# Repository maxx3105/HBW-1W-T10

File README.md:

# HBW-1W-T10

10-Kanal-1-Wire-Temperaturmodul für HomeMatic Wired

## Überblick

HomeMatic-Wired-Gerät (RS485) mit bis zu 10 DS18x20-Temperatursensoren an einem
gemeinsamen 1-Wire-Bus. Die Sensoren werden **automatisch erkannt**: Beim Start
scannt das Gerät den Bus, übernimmt die ROM-Adressen jedes gefundenen Fühlers und
legt sie in freie Kanäle. In der CCU wird nur noch eingestellt, wann gesendet wird.

Gerätetyp `0x81`, Aufbau auf zwei Platinen (Hauptplatine und Bedienplatine).

### Basiert auf:
- **HBWired** von Thorsten Pferdekaemper: https://github.com/ThorstenPferdekaemper/HBWired
- Sketch-Vorlage von **loetmeister.de** (Thorsten Pferdekaemper, Dirk Hoffmann)
- Identify-LED nach einer Idee von **jfische**: https://github.com/jfische/HBW-1W-T10

## Aufbau des Repositories

```
HBW-1W-T10/
├── HBW-1W-T10/                  Arduino-Sketch (Ordnername muss zur .ino passen)
│   ├── HBW-1W-T10.ino
│   └── HBW-1W-T10_config.h      Pinbelegung dieser Platine
├── hbw_1w_t10_v1.xml            CCU-Gerätedefinition (hs485types)
├── PlatineA_CNMB2/              KiCad-Projekt Hauptplatine (+ Gerber)
├── PlatineB_CNMB2/              KiCad-Projekt Bedienplatine (+ Gerber)
└── README.md
```

## Hardware

### Unterstützte Sensoren

| Sensor | Family-Code | Auflösung | Genauigkeit |
|--------|-------------|-----------|-------------|
| **DS18B20** | 0x28 | 9–12 Bit (Werksvorgabe 12) | ±0,5 °C |
| **DS18S20** / DS1820 | 0x10 | 9 Bit + Extended Resolution | ±0,5 °C |
| **DS1822** | 0x22 | 9–12 Bit | ±2 °C |
| **DS1825** | 0x3B | 9–12 Bit | ±0,5 °C |

Bis zu 10 Fühler parallel an einem Bus (Daten, VCC, GND). DS18S20 wird intern
anders umgerechnet als die übrigen — er liefert 9 Bit in 0,5-°C-Schritten, die
über COUNT_REMAIN auf volle Auflösung hochgerechnet werden.

> **DS1825** setzt einen kleinen Patch in HBWired voraus, siehe [Installation](#2-ds1825-freischalten-optional).

### Bauteile

**PlatineA_CNMB2** (Hauptplatine)
- **ATmega328P-A** mit 16-MHz-Resonator
- **MAX487E** RS485-Transceiver (10 kΩ nach GND an TXEN, damit der Treiber beim
  Reset nicht sendet)
- **MC34063AD** Step-Down-Wandler (24 V Bus → 5 V), 270 µH, SB140
- Feinsicherung 375 mA, SM4007 Verpolschutz
- AVR-ISP-6 Programmierstecker
- Schraubklemmen für 24 V und Bus
- 4,7 kΩ Pull-up am 1-Wire-Bus, 100 kΩ Pull-up am Taster

**PlatineB_CNMB2** (Bedienplatine)
- Status-LED (rot) und Identify-LED (blau), je 470 Ω
- Taster für Config/Werksreset sowie Reset
- Steckverbinder zur Hauptplatine

## Pinbelegung

| Pin | Netz im Schaltplan | Funktion |
|-----|--------------------|----------|
| D2 | `TXEN` | RS485 Transmit-Enable |
| D10 | `1WIRE` | 1-Wire-Datenleitung (4,7 kΩ Pull-up nach VCC) |
| D12 / PB4 | `ID_LED` | Identify-LED |
| D13 | `LED` | Status-LED |
| A6 | `Button` | Taster für Config/Werksreset (100 kΩ Pull-up nach VCC, Taster gegen GND) |
| D0 / D1 | `RXD` / `TXD` | UART0 zum MAX487E |

Die SoftwareSerial-Variante von HBWired kommt hier
nicht in Frage (die bräuchte D2 als TX) — das Modul läuft mit
`USE_HARDWARE_SERIAL` über UART0.

**A6** ist beim ATmega328P im TQFP-Gehäuse ein reiner ADC-Eingang: kein
digitaler Eingangspuffer, kein interner Pull-up, `digitalRead()` funktioniert
dort nicht. HBWired erkennt das und fragt den Taster über `analogRead() < 250`
ab (rund 1,22 V bei 5 V), was den externen 100-kΩ-Pull-up auf der Hauptplatine
voraussetzt.

## Funktionsumfang

### Konfiguration je Kanal (in CCU/FHEM)

| Parameter | Bereich | Vorgabe | Bedeutung |
|-----------|---------|---------|-----------|
| **ONEWIRE_TYPE** | NOT_USED / DS18B20 / DS18S20 / DS1822 / DS1825 / REMOVE_SENSOR | NOT_USED | Anzeige des erkannten Sensortyps; `REMOVE_SENSOR` gibt den Kanal wieder frei |
| **SEND_DELTA_TEMP** | 0,1–25,0 °C | 0,5 °C | Sendet, sobald sich die Temperatur um diesen Betrag ändert |
| **OFFSET** | −1,27 bis +1,27 °C | 0,0 °C | Kalibrier-Offset (vorzeichenbehaftet, mit Bias 127 gespeichert) |
| **SEND_MIN_INTERVAL** | 5–3600 s | 10 s | Mindestabstand zwischen zwei Sendungen |
| **SEND_MAX_INTERVAL** | 5–3600 s | 150 s | Spätestens nach dieser Zeit wird gesendet |

### Konfiguration des Geräts

| Parameter | Vorgabe | Bedeutung |
|-----------|---------|-----------|
| **IDENTIFY_LED** | aus | LED an D12 blinkt im 600-ms-Takt, solange gesetzt — zum Auffinden des Moduls in der Verteilung |
| **OWN_ADDRESS** | 1 | Busadresse des Geräts |

### ONEWIRE_TYPE ist kein Einstellwert

Der Parameter liegt auf dem ersten Byte der 1-Wire-ROM-Adresse — dem Family-Code.
Er zeigt also an, was der Bus-Scan gefunden hat, und wird nicht von Hand gesetzt:
Ein hier eingetragener Typ ändert nur dieses eine Byte, die restlichen sieben
(Seriennummer und CRC) bleiben stehen, und der Kanal spricht danach eine Adresse
an, die es auf dem Bus nicht gibt.

Sinnvoll zu benutzen ist einzig **`REMOVE_SENSOR`**: Das schreibt 0xFF, macht die
gespeicherte Adresse ungültig und gibt den Kanal für einen neuen Fühler frei. Beim
Zurücklesen steht dort anschließend `NOT_USED` — es ist ein einmaliger Befehl,
kein Zustand.

### Ablauf

1. **Bus-Scan** bei jedem Start und nach jedem Konfigurationsschreiben der
   Zentrale: neue Sensoren wandern in freie Kanäle, ihre ROM-Adresse wird ins
   EEPROM übernommen.
2. **Messung**: Alle 1200 ms ist ein Kanal an der Reihe — erst Konvertierung
   anstoßen, im nächsten Durchgang das Ergebnis lesen. Es läuft immer nur eine
   Konvertierung gleichzeitig auf dem gemeinsamen Bus.
3. **Sendeentscheidung**: nie vor SEND_MIN_INTERVAL; gesendet wird bei einer
   Änderung ≥ SEND_DELTA_TEMP oder spätestens nach SEND_MAX_INTERVAL.

Die Kanalzuordnung ergibt sich aus der Reihenfolge, in der die Sensoren beim Scan
gefunden werden — und die hängt an den ROM-Adressen, nicht an der Position im
Strang. Wer eine bestimmte Zuordnung braucht, steckt die Fühler einzeln
nacheinander an oder räumt Kanäle gezielt über `REMOVE_SENSOR` frei.

## Installation

### 1. Arduino-IDE vorbereiten
```bash
git clone https://github.com/maxx3105/HBWired
# nach Arduino/libraries/HBWired kopieren
```

### 2. DS1825 freischalten (optional)

DS18B20, DS18S20 und DS1822 laufen mit HBWired unverändert. Für den **DS1825**
sind zwei kleine Ergänzungen in der Bibliothek nötig, da sie den Family-Code sonst
verwirft:

`libraries/src/HBWOneWireTempSensors.h`
```diff
     static const uint8_t DS18B20_ID = 0x28;
+    static const uint8_t DS1825_ID = 0x3B;
```

`libraries/src/HBWOneWireTempSensors.cpp`
```diff
 bool HBWOneWireTemp::deviceInvalidOrEmptyID(uint8_t deviceType) {
-  return !((deviceType == DS18B20_ID) || (deviceType == DS18S20_ID) || (deviceType == DS1822_ID));
+  return !((deviceType == DS18B20_ID) || (deviceType == DS18S20_ID) || (deviceType == DS1822_ID) ||
+           (deviceType == DS1825_ID));
 };
```

Die Umrechnung braucht keinen eigenen Zweig: Der DS1825 hält seine
Auflösungsbits an derselben Stelle wie der DS18B20 (`data[4] & 0x60`), womit der
bestehende `else`-Zweig greift.

### 3. Übersetzen und flashen

Der Sketch liegt im Unterordner `HBW-1W-T10/` (der Ordnername muss dem
`.ino`-Namen entsprechen).

- `HBW-1W-T10/HBW-1W-T10.ino` in der Arduino-IDE öffnen
- Board: **Arduino Nano** (ATmega328P)
- `HBW-1W-T10_config.h` bildet die Platine ab; `USE_HARDWARE_SERIAL` ist gesetzt.
  Zum Testen auf einem Nano mit Debug-Ausgabe auskommentieren.
- Flashen über ISP

Oder aus dem Projektverzeichnis heraus:

```
arduino-cli compile --fqbn arduino:avr:nano:cpu=atmega328 HBW-1W-T10
arduino-cli compile --fqbn arduino:avr:nano:cpu=atmega328 --upload --programmer usbasp HBW-1W-T10
```

Hinweis: Ist die EESAVE-Fuse nicht gesetzt, löscht jeder ISP-Flash das EEPROM —
und damit die Busadresse und alle gespeicherten Sensoradressen.

### 4. CCU/RaspberryMatic einrichten
1. https://github.com/maxx3105/JP-HB-Devices-addon
2. JP-HB-Devices-addon installieren
3. Gerät an den RS485-Bus anschließen
4. Anlernen und aus dem Posteingang übernehmen

## EEPROM-Belegung

`HBWDevice` liest die Konfigurationsstruktur ab EEPROM-Adresse `0x01`
(siehe `readConfig()` in HBWired.cpp), Struktur-Offset 6 landet also auf `0x07`.

```
0x00      : ungenutzt
0x01      : Logging-Zeit
0x02-0x05 : Zentralen-Adresse
0x06      : Bit 0 Direct-Link-Flag, Bit 1 Identify-LED (invertiert gespeichert)
0x07      : Kanal 1, Konfiguration (14 Byte)
  +0: send_delta_temp
  +1: offset (Bias 127: 0 = −1,27 °C, 127 = 0,00 °C, 254 = +1,27 °C)
  +2-3: send_min_interval (16 Bit, little endian)
  +4-5: send_max_interval (16 Bit, little endian)
  +6-13: 1-Wire-ROM-Adresse; Byte +6 ist der Family-Code = ONEWIRE_TYPE
0x15/0x23/... : Kanal 2..10, Konfiguration (Schrittweite 14), bis 0x92
0x3FC-0x3FF : OWN_ADDRESS (Busadresse, E2END−3 beim 1-kB-EEPROM des 328P)
```

Die Identify-LED wird **invertiert** abgelegt (`boolean_integer invert="true"` in
der XML): Nach einem Werksreset steht das EEPROM auf 0xFF, das Flag also auf 1 —
und die LED bleibt aus. Deshalb heißt das Feld im Sketch `n_identify_led`.

Ein `static_assert` in `HBW-1W-T10.ino` koppelt `ADDRESS_START_CONF_TEMP_CHAN` an
die tatsächliche Position von `TempOWCfg` in der Struktur. Käme ein Feld davor
hinzu, würde `sensorSearch()` sonst still in die Kanalkonfiguration schreiben —
der Build bricht stattdessen ab.

## Fehlersuche

### Sensoren werden nicht gefunden
- Verdrahtung prüfen (3-adrig, kein Parasite-Power-Betrieb vorgesehen)
- Nach dem Anstecken Reset drücken oder in der CCU die Konfiguration schreiben —
  beides löst einen Bus-Scan aus
- Fremde 1-Wire-Bausteine am Bus belegen kurzzeitig einen Kanal, bis ein echter
  Fühler den Platz übernimmt

### Temperatur zeigt −273,15 °C oder −273,14 °C
Das sind die beiden Sonderwerte der Firmware: **−273,15 °C** heißt „Kanal ohne
gültigen Sensor", **−273,14 °C** steht für einen Lese- oder CRC-Fehler, der drei
Versuche überdauert hat — typisch bei abgezogenem Fühler, zu langer Leitung oder
fehlendem Pull-up.

### Falsche Kanalzuordnung
Erwartungsgemäß: Die Reihenfolge kommt vom Bus-Scan, nicht von der Verdrahtung.
Über `REMOVE_SENSOR` einzelne Kanäle freiräumen und die Fühler nacheinander
anstecken.

### Gerät kommuniziert nicht
- RS485-Verdrahtung prüfen (A/B nicht vertauscht)
- Busadresse gesetzt? (`OWN_ADDRESS`, Seriennummer ist 7-Stellig und darf nur einmal am Bus vorhanden sein)
- Ist `USE_HARDWARE_SERIAL` aktiv? Ohne die Option belegt SoftwareSerial D2, das
  auf dieser Platine das Transmit-Enable ist.

### Modul in der Verteilung finden
`IDENTIFY_LED` in der Gerätekonfiguration setzen — die LED an D12 blinkt dann im
600-ms-Takt, bis der Haken wieder entfernt wird.

## Lizenz

Creative Commons BY-NC-SA 3.0 AT
http://creativecommons.org/licenses/by-nc-sa/3.0/at/

## Dank an

- Thorsten Pferdekaemper – HBWired-Framework
- Dirk Hoffmann – Beiträge zu HBWired
- loetmeister.de – Sketch-Vorlage HBW-1W-T10
- jfische – Idee der Identify-LED

## Änderungsverlauf

### v0.06
- 1-Wire-Busarbitrierung repariert: Die Kanäle hielten Zeiger auf lokale
  Variablen von `setup()`, deren Speicher freigegeben wird, sobald `loop()`
  läuft (auch upstream eingereicht:
  [HBWired#47](https://github.com/ThorstenPferdekaemper/HBWired/pull/47))
- `static_assert` koppelt die Kanaladresse an das Struktur-Layout

### v0.05
- DS1825 als vierter Sensortyp

### v0.04
- Identify-LED an D12, schaltbar über den Geräteparameter `IDENTIFY_LED`

### v0.03
- Prüfung auf unterstützte Sensortypen
- Konvertierungs- und Messablauf entzerrt, um falsche Messwerte zu vermeiden

### v0.02
- Start und Fehlerbehandlung bei abgezogenen Sensoren verbessert

### v0.01
- Erste Fassung

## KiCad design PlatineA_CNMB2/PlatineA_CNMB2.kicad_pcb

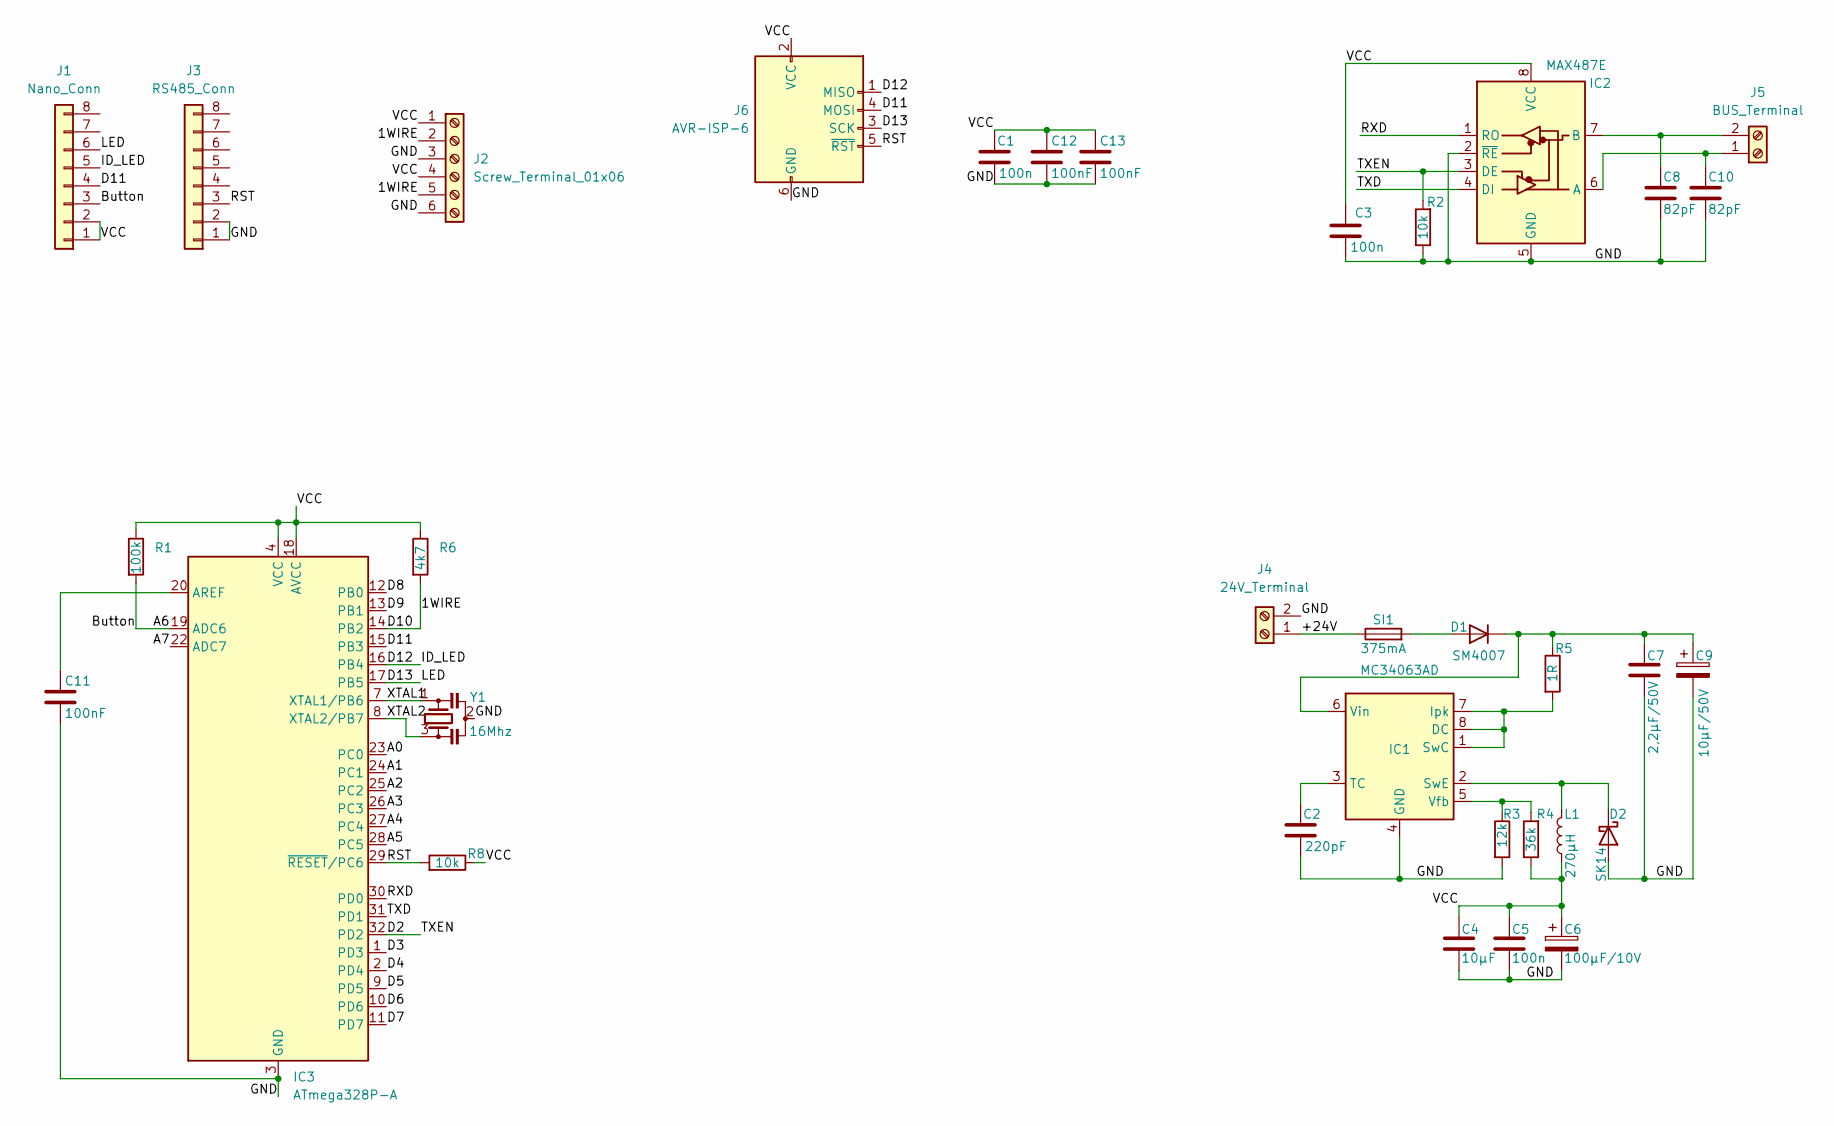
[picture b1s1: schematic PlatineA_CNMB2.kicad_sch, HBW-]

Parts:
C1, C3, C5: 100n; C_0805_2012Metric_Pad1.18x1.45mm_HandSolder
C2: 220pF; C_0805_2012Metric_Pad1.18x1.45mm_HandSolder
C4: 10µF; C_1210_3225Metric_Pad1.33x2.70mm_HandSolder
C6: 100µF/10V; CP_Radial_D5.0mm_P2.50mm
C7: 2,2µF/50V; C_1210_3225Metric_Pad1.33x2.70mm_HandSolder
C8, C10: 82pF; C_0805_2012Metric_Pad1.18x1.45mm_HandSolder
C9: 10µF/50V; CP_Radial_D5.0mm_P2.50mm
C11, C12, C13: 100nF; C_0805_2012Metric_Pad1.18x1.45mm_HandSolder
D1: SM4007; D_MELF
D2: SK14; D_SMA_Handsoldering
IC1: MC34063AD; SOIC-8_3.9x4.9mm_P1.27mm
IC2: MAX487E; SOIC-8_3.9x4.9mm_P1.27mm
IC3: ATmega328P-A; TQFP-32_7x7mm_P0.8mm
J1: Nano_Conn; PinHeader_1x08_P2.54mm_Vertical
J2: Screw_Terminal_01x06; TerminalBlock_bornier-6_P5.08mm
J3: RS485_Conn; PinHeader_1x08_P2.54mm_Vertical
J4: 24V_Terminal; TerminalBlock_bornier-2_P5.08mm
J5: BUS_Terminal; TerminalBlock_bornier-2_P5.08mm
J6: AVR-ISP-6; PinHeader_2x03_P2.54mm_Vertical
L1: 270µH; L_Taiyo-Yuden_MD-4040
R1: 100k; R_0805_2012Metric_Pad1.20x1.40mm_HandSolder
R2, R8: 10k; R_0805_2012Metric_Pad1.20x1.40mm_HandSolder
R3: 12k; R_0805_2012Metric_Pad1.20x1.40mm_HandSolder
R4: 36k; R_0805_2012Metric_Pad1.20x1.40mm_HandSolder
R5: 1R; R_0805_2012Metric_Pad1.20x1.40mm_HandSolder
R6: 4k7; R_0805_2012Metric_Pad1.20x1.40mm_HandSolder
SI1: 375mA; FUSC6127X294N
Y1: 16Mhz; Resonator_SMD_Murata_CSTxExxV-3Pin_3.0x1.1mm_HandSoldering

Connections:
/1WIRE: IC3.14 (PB2), J2.2, J2.5, R6.2
/+24V: J4.1, SI1.1
/A0: IC3.23 (PC0)
/A1: IC3.24 (PC1)
/A2: IC3.25 (PC2)
/A3: IC3.26 (PC3)
/A4: IC3.27 (PC4)
/A5: IC3.28 (PC5)
/A6: IC3.19 (ADC6), J1.3, R1.2
/A7: IC3.22 (ADC7)
/D2: IC2.3 (DE), IC3.32 (PD2), R2.2
/D3: IC3.1 (PD3)
/D4: IC3.2 (PD4)
/D5: IC3.9 (PD5)
/D6: IC3.10 (PD6)
/D7: IC3.11 (PD7)
/D8: IC3.12 (PB0)
/D9: IC3.13 (PB1)
/D11: IC3.15 (PB3), J1.4, J6.4 (MOSI)
/D12: IC3.16 (PB4), J1.5, J6.1 (MISO)
/D13: IC3.17 (PB5), J1.6, J6.3 (SCK)
/GND: C1.2, C2.2, C3.1, C4.2, C5.1, C6.2, C7.2, C8.2, C9.2, C10.2, C11.1, C12.1, C13.1, D2.2 (A), IC1.4 (GND), IC2.2 (~RE), IC2.5 (GND), IC3.3 (GND), IC3.5 (GND), IC3.21 (GND), J2.3, J2.6, J3.1, J3.2, J4.2, J6.6 (GND), R2.1, R3.2, Y1.2
/RST: IC3.29 (~RESET/PC6), J3.3, J6.5 (~RST), R8.2
/RXD: IC2.1 (RO), IC3.30 (PD0)
/TXD: IC2.4 (DI), IC3.31 (PD1)
/VCC: C1.1, C3.2, C4.1, C5.2, C6.1, C12.2, C13.2, IC2.8 (VCC), IC3.4 (VCC), IC3.6 (VCC), IC3.18 (AVCC), J1.1, J1.2, J2.1, J2.4, J6.2 (VCC), L1.1, R1.1, R4.1, R6.1, R8.1
/XTAL1: IC3.7 (XTAL1/PB6), Y1.1
/XTAL2: IC3.8 (XTAL2/PB7), Y1.3
unnamed: D1.2 (A), SI1.2
unnamed: C7.1, C9.1, D1.1 (K), IC1.6 (Vin), R5.1
unnamed: D2.1 (K), IC1.2 (SwE), L1.2
unnamed: IC1.1 (SwC), IC1.7 (Ipk), IC1.8 (DC), R5.2
unnamed: C2.1, IC1.3 (TC)
unnamed: IC1.5 (Vfb), R3.1, R4.2
unnamed: C10.1, IC2.6 (A), J5.1
unnamed: C8.1, IC2.7 (B), J5.2
unnamed: C11.2, IC3.20 (AREF)

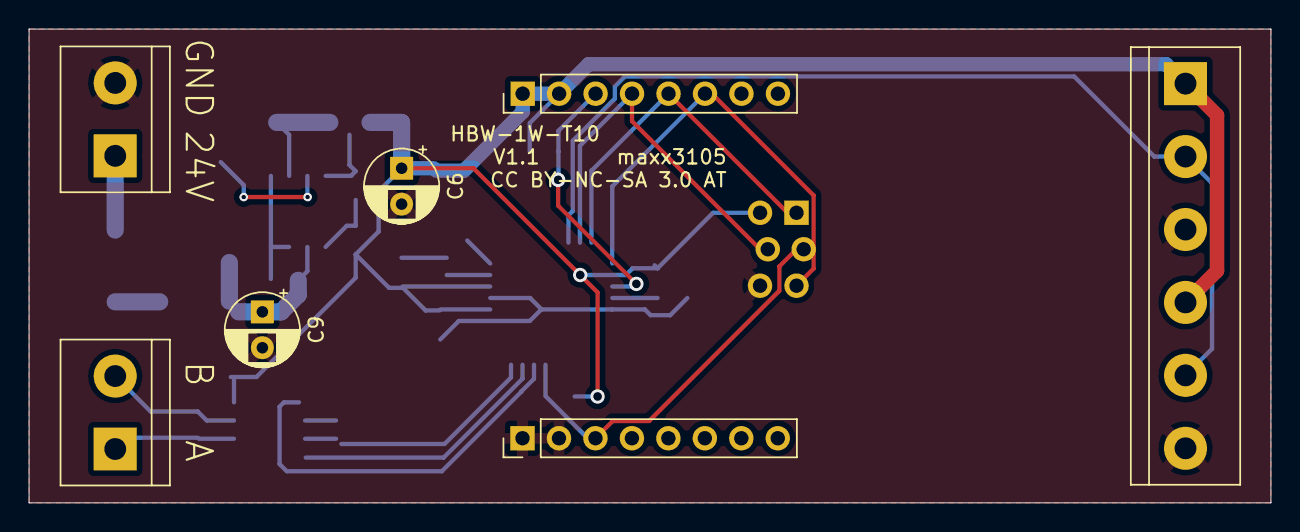
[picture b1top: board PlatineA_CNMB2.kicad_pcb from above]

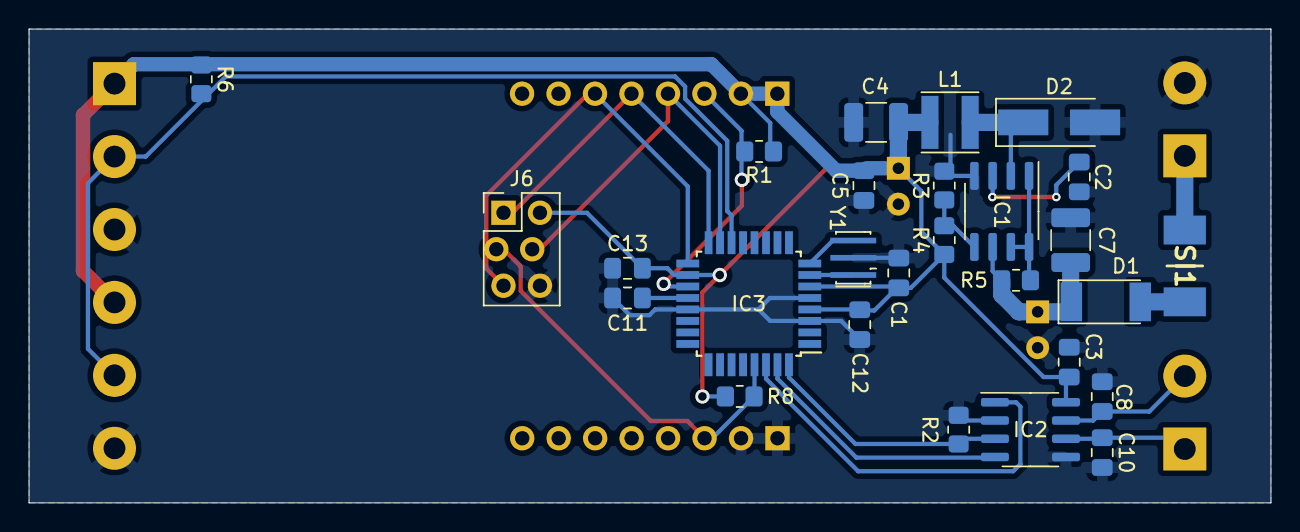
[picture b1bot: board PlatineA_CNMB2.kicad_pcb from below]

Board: 2 copper layers, 86.5 x 33.0 mm, 34 parts (27 on the bottom side), 23 nets.

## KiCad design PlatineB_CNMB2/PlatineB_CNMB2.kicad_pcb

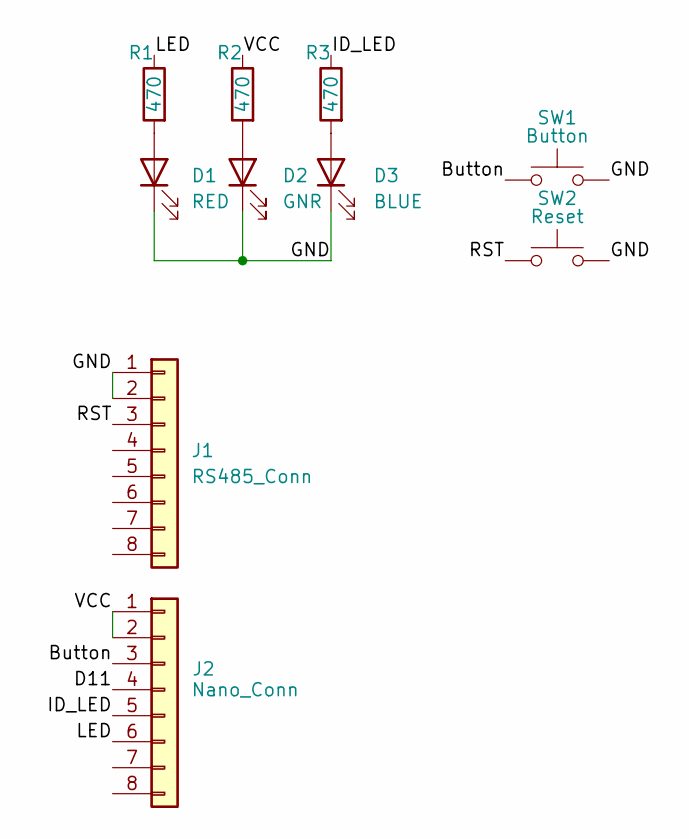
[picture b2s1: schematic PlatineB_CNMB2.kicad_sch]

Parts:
D1: RED; LED_D5.0mm
D2: GNR; LED_D5.0mm
D3: BLUE; LED_D5.0mm
J1: RS485_Conn; PinHeader_1x08_P2.54mm_Vertical
J2: Nano_Conn; PinSocket_1x08_P2.54mm_Vertical
R1, R2, R3: 470; R_0805_2012Metric_Pad1.20x1.40mm_HandSolder
SW1: Button; SW_PUSH_6mm_H13mm
SW2: Reset; SW_PUSH_6mm_H13mm

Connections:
/Button: J2.3, SW1.1
/D11: J2.4
/GND: D1.1 (K), D2.1 (K), D3.1 (K), J1.1, J1.2, SW1.2, SW2.2
/ID_LED: J2.5, R3.1
/LED: J2.6, R1.1
/RST: J1.3, SW2.1
/VCC: J2.1, J2.2, R2.1
unnamed: D1.2 (A), R1.2
unnamed: D2.2 (A), R2.2
unnamed: D3.2 (A), R3.2

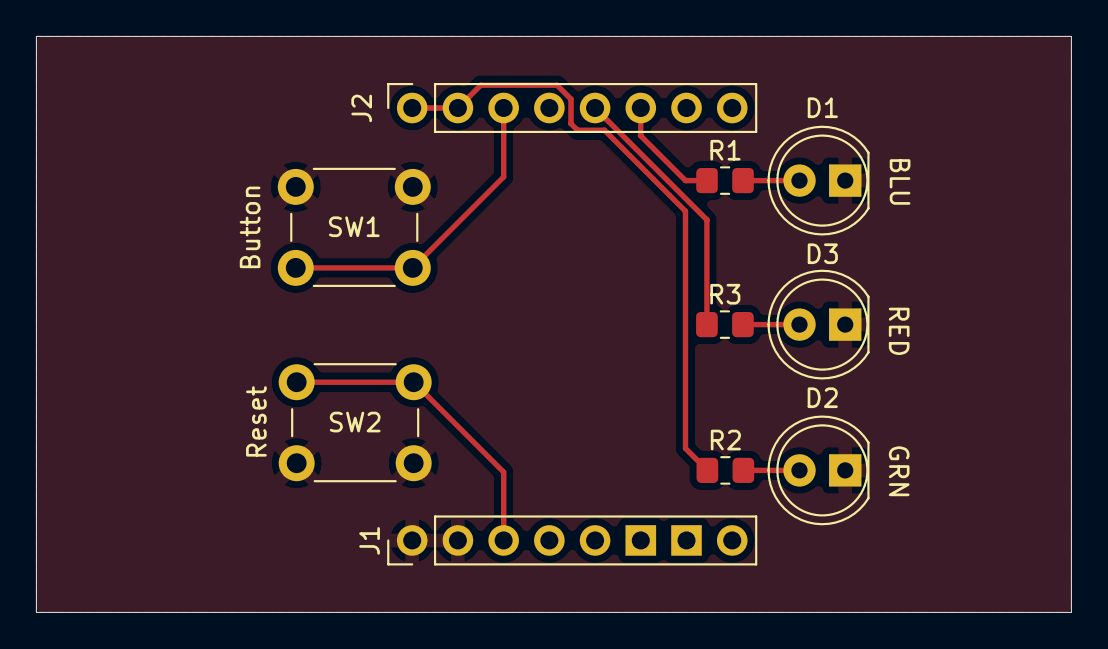
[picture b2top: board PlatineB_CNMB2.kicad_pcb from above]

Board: 2 copper layers, 57.5 x 32.0 mm, 10 parts (0 on the bottom side), 9 nets.

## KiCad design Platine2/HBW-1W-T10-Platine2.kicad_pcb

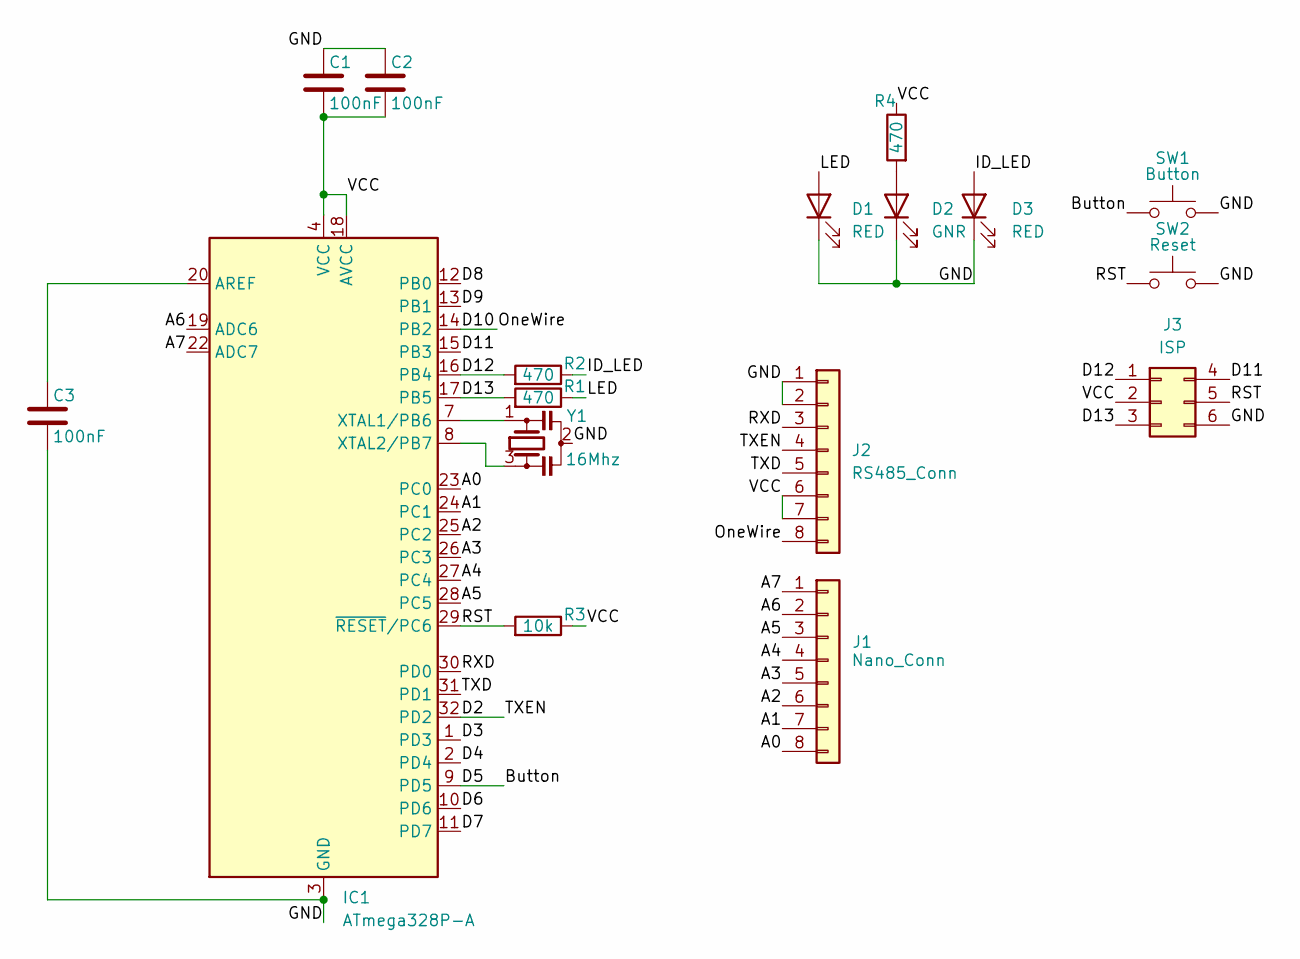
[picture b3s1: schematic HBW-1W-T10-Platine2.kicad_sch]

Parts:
C1, C2, C3: 100nF; C_0805_2012Metric_Pad1.18x1.45mm_HandSolder
D1, D3: RED; LED_D5.0mm
D2: GNR; LED_D5.0mm
IC1: ATmega328P-A; TQFP-32_7x7mm_P0.8mm
J1: Nano_Conn; PinSocket_1x08_P2.54mm_Vertical
J2: RS485_Conn; PinHeader_1x08_P2.54mm_Vertical
J3: ISP; PinHeader_2x03_P2.54mm_Vertical
R1, R2, R4: 470; R_0805_2012Metric_Pad1.20x1.40mm_HandSolder
R3: 10k; R_0805_2012Metric_Pad1.20x1.40mm_HandSolder
SW1: Button; SW_PUSH_6mm_H13mm
SW2: Reset; SW_PUSH_6mm_H13mm
Y1: 16Mhz; Resonator_SMD_Murata_CSTxExxV-3Pin_3.0x1.1mm_HandSoldering

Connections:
/A0: IC1.23 (PC0), J1.8
/A1: IC1.24 (PC1), J1.7
/A2: IC1.25 (PC2), J1.6
/A3: IC1.26 (PC3), J1.5
/A4: IC1.27 (PC4), J1.4
/A5: IC1.28 (PC5), J1.3
/A6: IC1.19 (ADC6), J1.2
/A7: IC1.22 (ADC7), J1.1
/D2: IC1.32 (PD2), J2.4
/D3: IC1.1 (PD3)
/D4: IC1.2 (PD4)
/D5: IC1.9 (PD5), SW1.1
/D6: IC1.10 (PD6)
/D7: IC1.11 (PD7)
/D8: IC1.12 (PB0)
/D9: IC1.13 (PB1)
/D10: IC1.14 (PB2), J2.8
/D11: IC1.15 (PB3), J3.4
/D12: IC1.16 (PB4), J3.1, R2.2
/D13: IC1.17 (PB5), J3.3, R1.2
/GND: C1.2, C2.2, C3.1, D1.1 (K), D2.1 (K), D3.1 (K), IC1.3 (GND), IC1.5 (GND), IC1.21 (GND), J2.1, J2.2, J3.6, SW1.2, SW2.2, Y1.2
/ID_LED: D3.2 (A), R2.1
/LED: D1.2 (A), R1.1
/RST: IC1.29 (~RESET/PC6), J3.5, R3.2, SW2.1
/RXD: IC1.30 (PD0), J2.3
/TXD: IC1.31 (PD1), J2.5
/VCC: C1.1, C2.1, IC1.4 (VCC), IC1.6 (VCC), IC1.18 (AVCC), J2.6, J2.7, J3.2, R3.1, R4.1
unnamed: C3.2, IC1.20 (AREF)
unnamed: D2.2 (A), R4.2
unnamed: IC1.7 (XTAL1/PB6), Y1.1
unnamed: IC1.8 (XTAL2/PB7), Y1.3

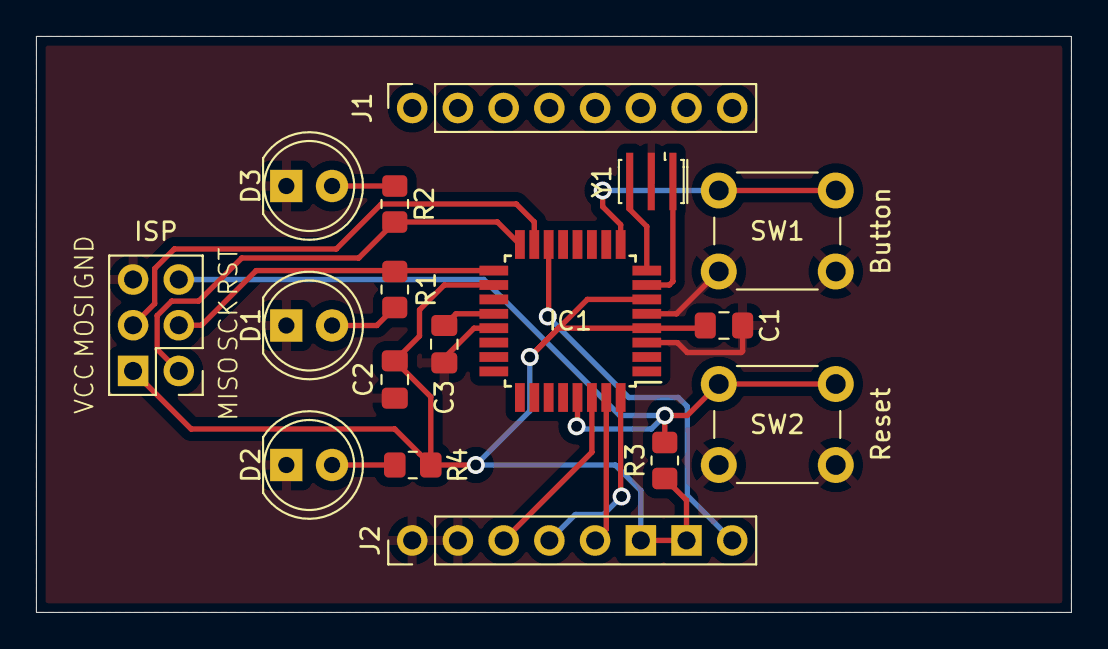
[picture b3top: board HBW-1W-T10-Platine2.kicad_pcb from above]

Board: 2 copper layers, 57.5 x 32.0 mm, 17 parts (0 on the bottom side), 25 nets.

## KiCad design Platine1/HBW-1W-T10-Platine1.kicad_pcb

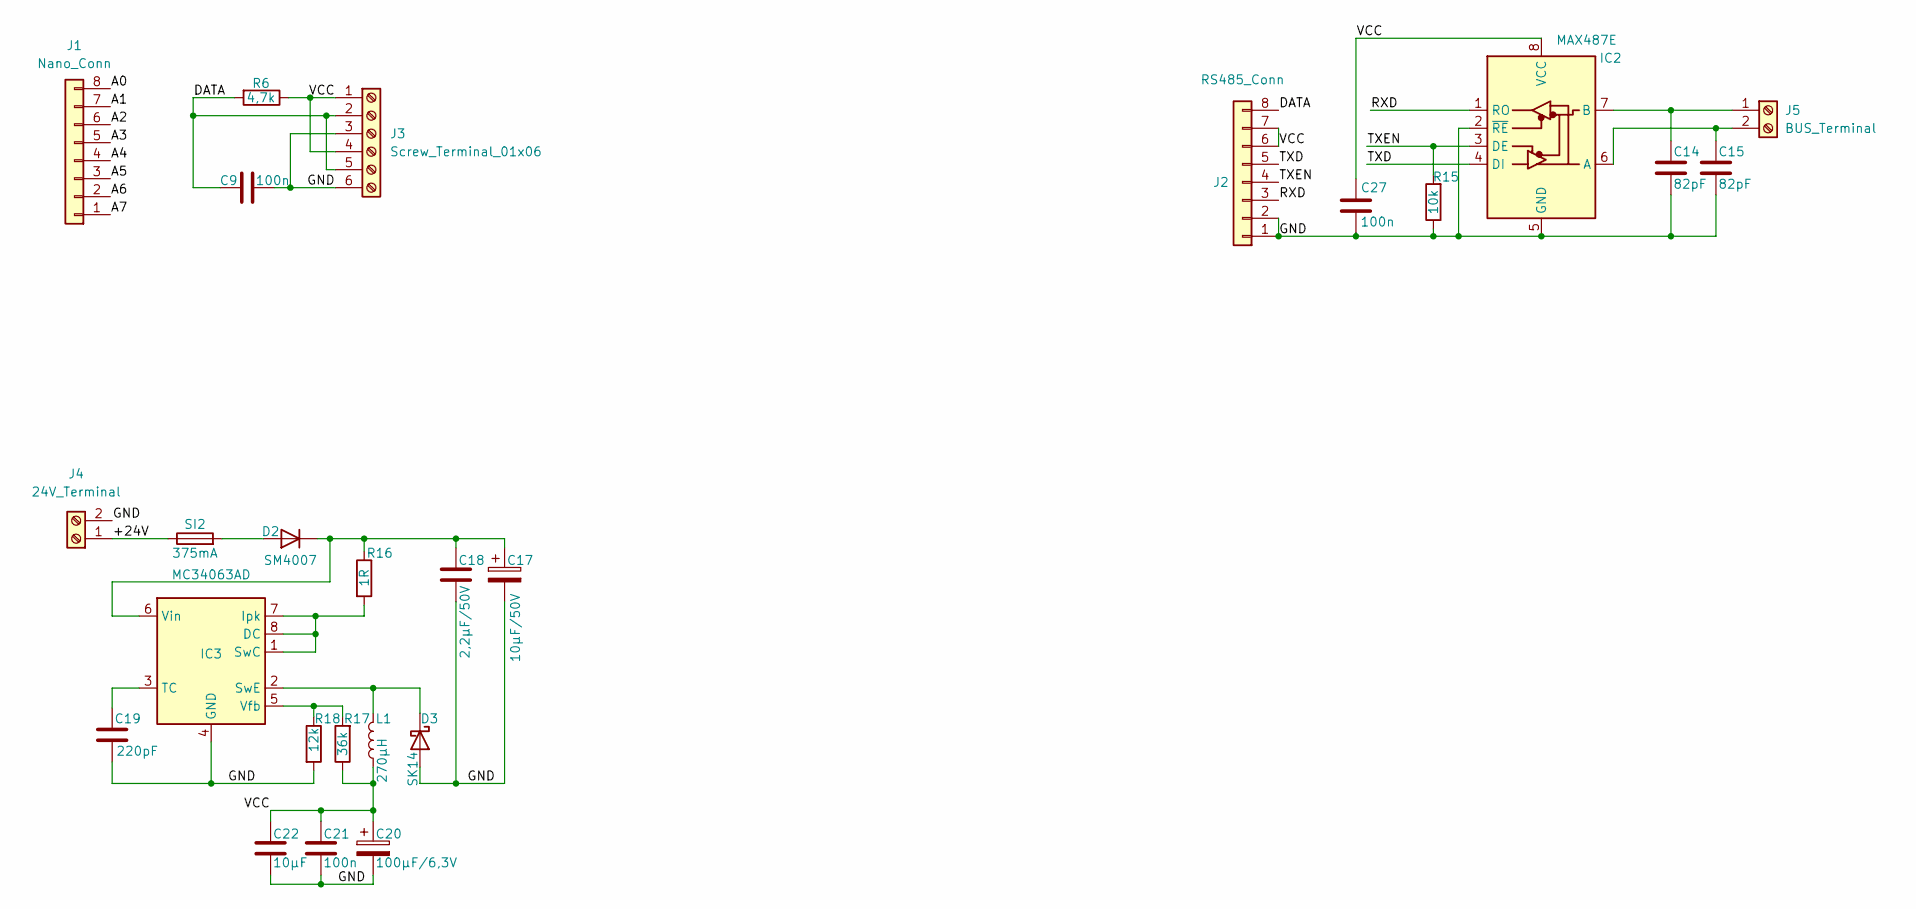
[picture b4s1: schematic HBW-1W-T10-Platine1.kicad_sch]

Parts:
C9, C21, C27: 100n; C_0805_2012Metric_Pad1.18x1.45mm_HandSolder
C14, C15: 82pF; C_0805_2012Metric_Pad1.18x1.45mm_HandSolder
C17: 10µF/50V; CP_Elec_6.3x5.8
C18: 2,2µF/50V; C_1210_3225Metric_Pad1.33x2.70mm_HandSolder
C19: 220pF; C_0805_2012Metric_Pad1.18x1.45mm_HandSolder
C20: 100µF/6,3V; CP_EIA-7343-20_Kemet-V_Pad2.25x2.55mm_HandSolder
C22: 10µF; C_1210_3225Metric_Pad1.33x2.70mm_HandSolder
D2: SM4007; D_MELF
D3: SK14; D_SMA_Handsoldering
IC2: MAX487E; SOIC-8_3.9x4.9mm_P1.27mm
IC3: MC34063AD; SOIC-8_3.9x4.9mm_P1.27mm
J1: Nano_Conn; PinHeader_1x08_P2.54mm_Vertical
J2: RS485_Conn; PinHeader_1x08_P2.54mm_Vertical
J3: Screw_Terminal_01x06; TerminalBlock_bornier-6_P5.08mm
J4: 24V_Terminal; TerminalBlock_bornier-2_P5.08mm
J5: BUS_Terminal; TerminalBlock_bornier-2_P5.08mm
L1: 270µH; L_Taiyo-Yuden_MD-4040
R6: 4,7k; R_0805_2012Metric_Pad1.20x1.40mm_HandSolder
R15: 10k; R_0805_2012Metric_Pad1.20x1.40mm_HandSolder
R16: 1R; R_0805_2012Metric_Pad1.20x1.40mm_HandSolder
R17: 36k; R_0805_2012Metric_Pad1.20x1.40mm_HandSolder
R18: 12k; R_0805_2012Metric_Pad1.20x1.40mm_HandSolder
SI2: 375mA; FUSC6127X294N

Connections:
/+24V: J4.1, SI2.1
/A0: J1.8
/A1: J1.7
/A2: J1.6
/A3: J1.5
/A4: J1.4
/A5: J1.3
/A6: J1.2
/A7: J1.1
/DATA: C9.1, J2.8, J3.2, J3.5, R6.2
/GND: C9.2, C14.2, C15.2, C17.2, C18.2, C19.2, C20.2, C21.1, C22.2, C27.1, D3.2 (A), IC2.2 (~RE), IC2.5 (GND), IC3.4 (GND), J2.1, J2.2, J3.3, J3.6, J4.2, R15.1, R18.2
/RXD: IC2.1 (RO), J2.3
/TXD: IC2.4 (DI), J2.5
/TXEN: IC2.3 (DE), J2.4, R15.2
/VCC: C20.1, C21.2, C22.1, C27.2, IC2.8 (VCC), J2.6, J2.7, J3.1, J3.4, L1.1, R6.1, R17.1
unnamed: C14.1, IC2.7 (B), J5.1
unnamed: C15.1, IC2.6 (A), J5.2
unnamed: C17.1, C18.1, D2.1 (K), IC3.6 (Vin), R16.1
unnamed: C19.1, IC3.3 (TC)
unnamed: D2.2 (A), SI2.2
unnamed: D3.1 (K), IC3.2 (SwE), L1.2
unnamed: IC3.1 (SwC), IC3.7 (Ipk), IC3.8 (DC), R16.2
unnamed: IC3.5 (Vfb), R17.2, R18.1

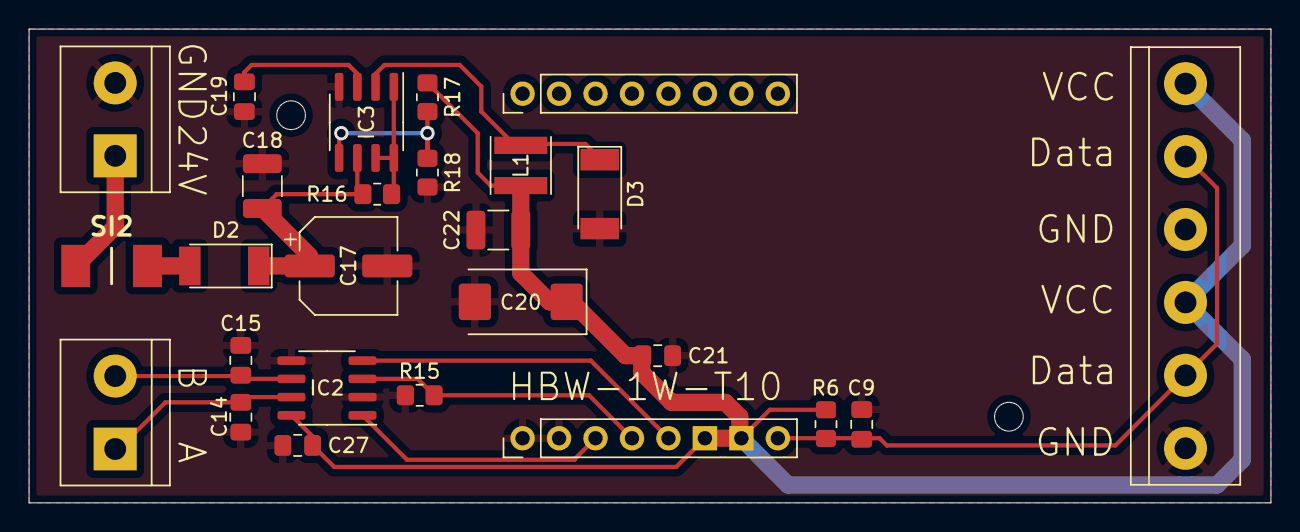
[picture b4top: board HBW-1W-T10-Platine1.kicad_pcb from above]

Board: 2 copper layers, 86.5 x 33.0 mm, 26 parts (0 on the bottom side), 15 nets.

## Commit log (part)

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2024-03-19 Change button from A6 to D5

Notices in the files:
PlatineA_CNMB2/PlatineA_CNMB2.kicad_pcb:
CC BY-NC-SA 3.0 AT
